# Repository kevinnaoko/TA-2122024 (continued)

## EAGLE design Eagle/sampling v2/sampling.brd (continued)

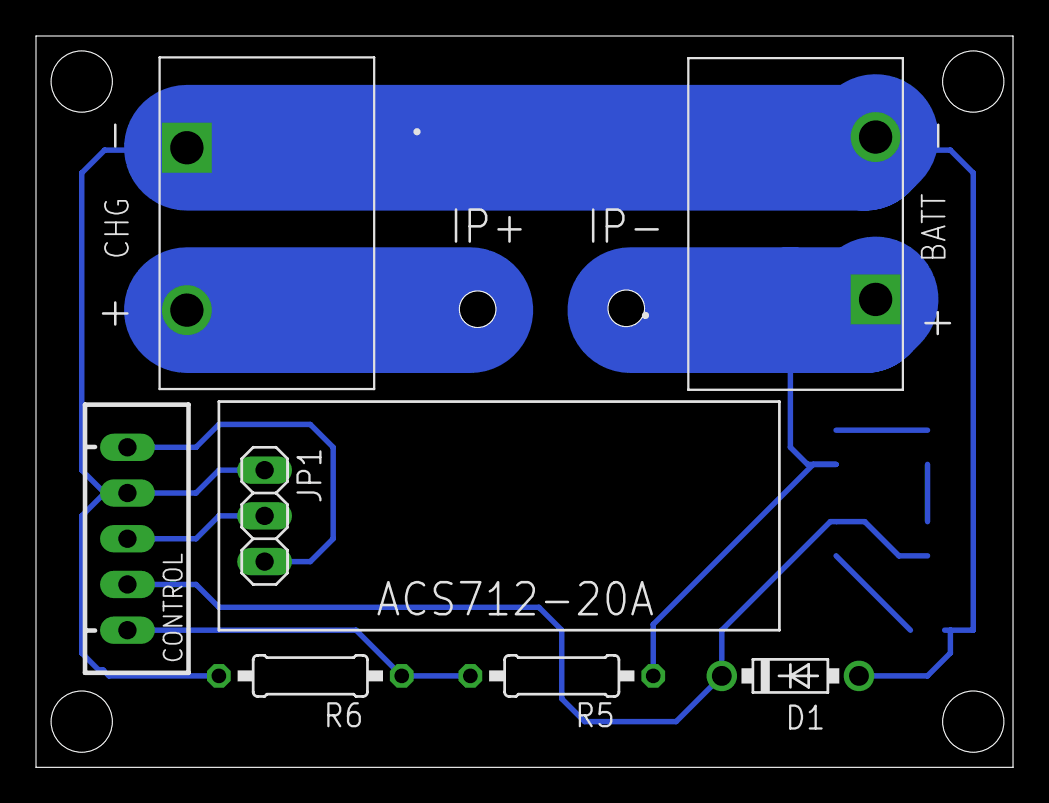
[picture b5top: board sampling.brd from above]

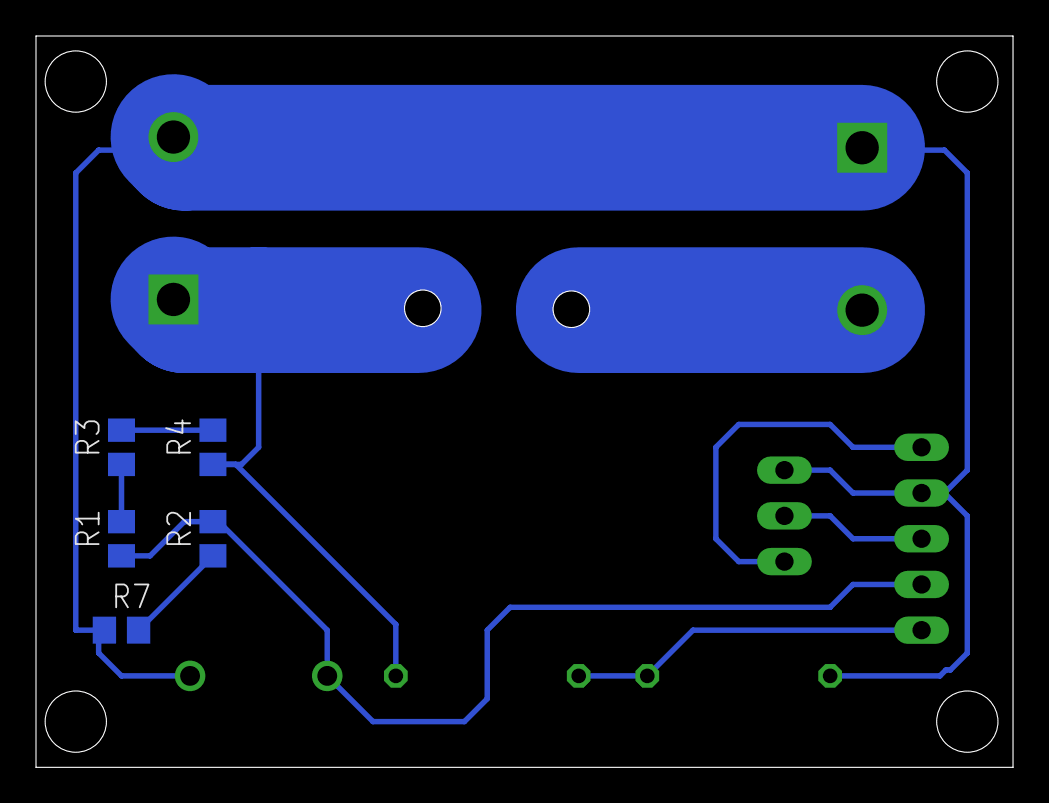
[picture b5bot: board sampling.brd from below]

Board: 2 copper layers, 54.3 x 40.6 mm, 12 parts (5 on the bottom side), 9 nets.

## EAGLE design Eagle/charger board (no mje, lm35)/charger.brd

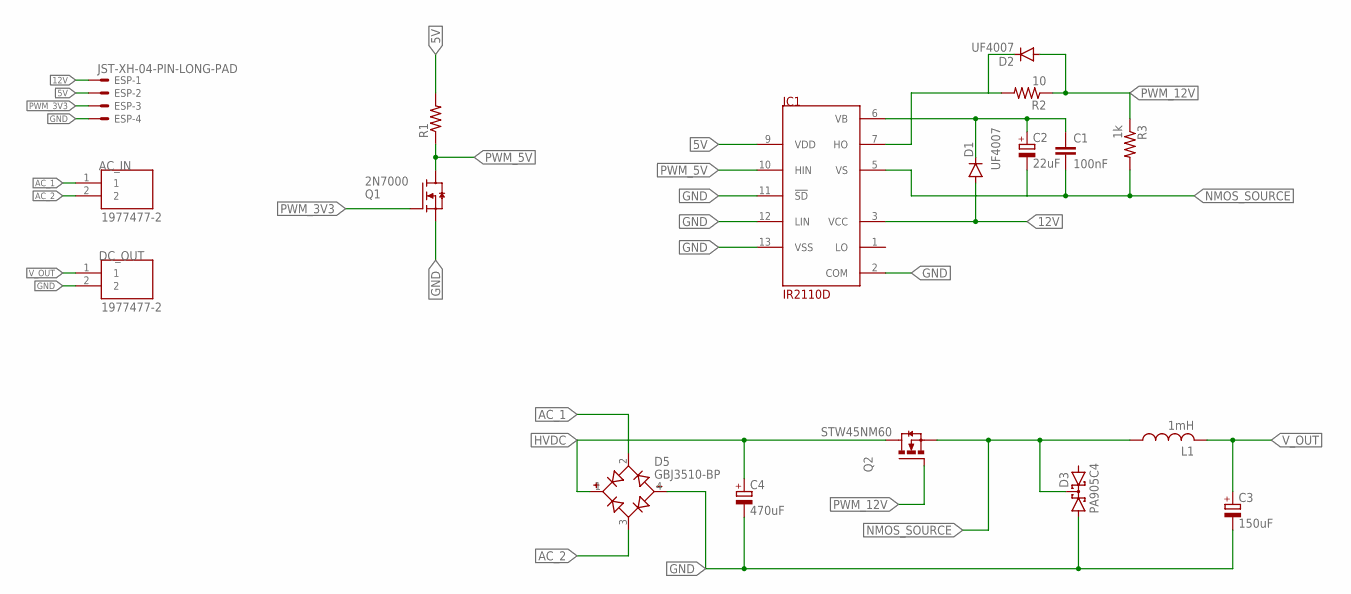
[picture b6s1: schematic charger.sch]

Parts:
AC_IN: 1977477-2; TE_1977477-2
C1: 100nF; C025-025X050
C2: 22uF; E2,5-6E
C3: 150uF; E7,5-18
C4: 470uF; EB35D
D1, D2: UF4007; DO34-7
D3: PA905C4; SOT93S
D5: GBJ3510-BP; DIOB_GBJ3510-BP
DC_OUT: 1977477-2; TE_1977477-2
ESP: JST-XH-04-PIN-LONG-PAD; JST-XH-04-PACKAGE-LONG-PAD
IC1: IR2110D; DIL14
L1: 1mH; TJ7-U1
Q1: 2N7000; TO92
Q2: STW45NM60; TO247AC
R1: R-US_0204/7; 0204/7
R2: 10; 0204/7
R3: 1k; 0204/7

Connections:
5V: ESP.2, IC1.9 (VDD), R1.2
12V: D1.A, ESP.1, IC1.3 (VCC)
AC_1: AC_IN.1, D5.2 (AC1)
AC_2: AC_IN.2, D5.3 (AC2)
GND: C3.-, C4.-, D3.A1, D5.4 (-), DC_OUT.2, ESP.4, IC1.2 (COM), IC1.11 (!SD), IC1.12 (LIN), IC1.13 (VSS), Q1.1 (S)
HVDC: C4.+, D5.1 (+), Q2.2 (D)
unnamed: D2.C, IC1.7 (HO), R2.2
NMOS_SOURCE: C1.2, C2.-, D3.C, IC1.5 (VS), L1.1, Q2.3 (S), R3.2
PWM_3V3: ESP.3, Q1.2 (G)
PWM_5V: IC1.10 (HIN), Q1.3 (D), R1.1
PWM_12V: D2.A, Q2.1 (G), R2.1, R3.1
VB: C1.1, C2.+, D1.C, IC1.6 (VB)
V_OUT: C3.+, DC_OUT.1, L1.2

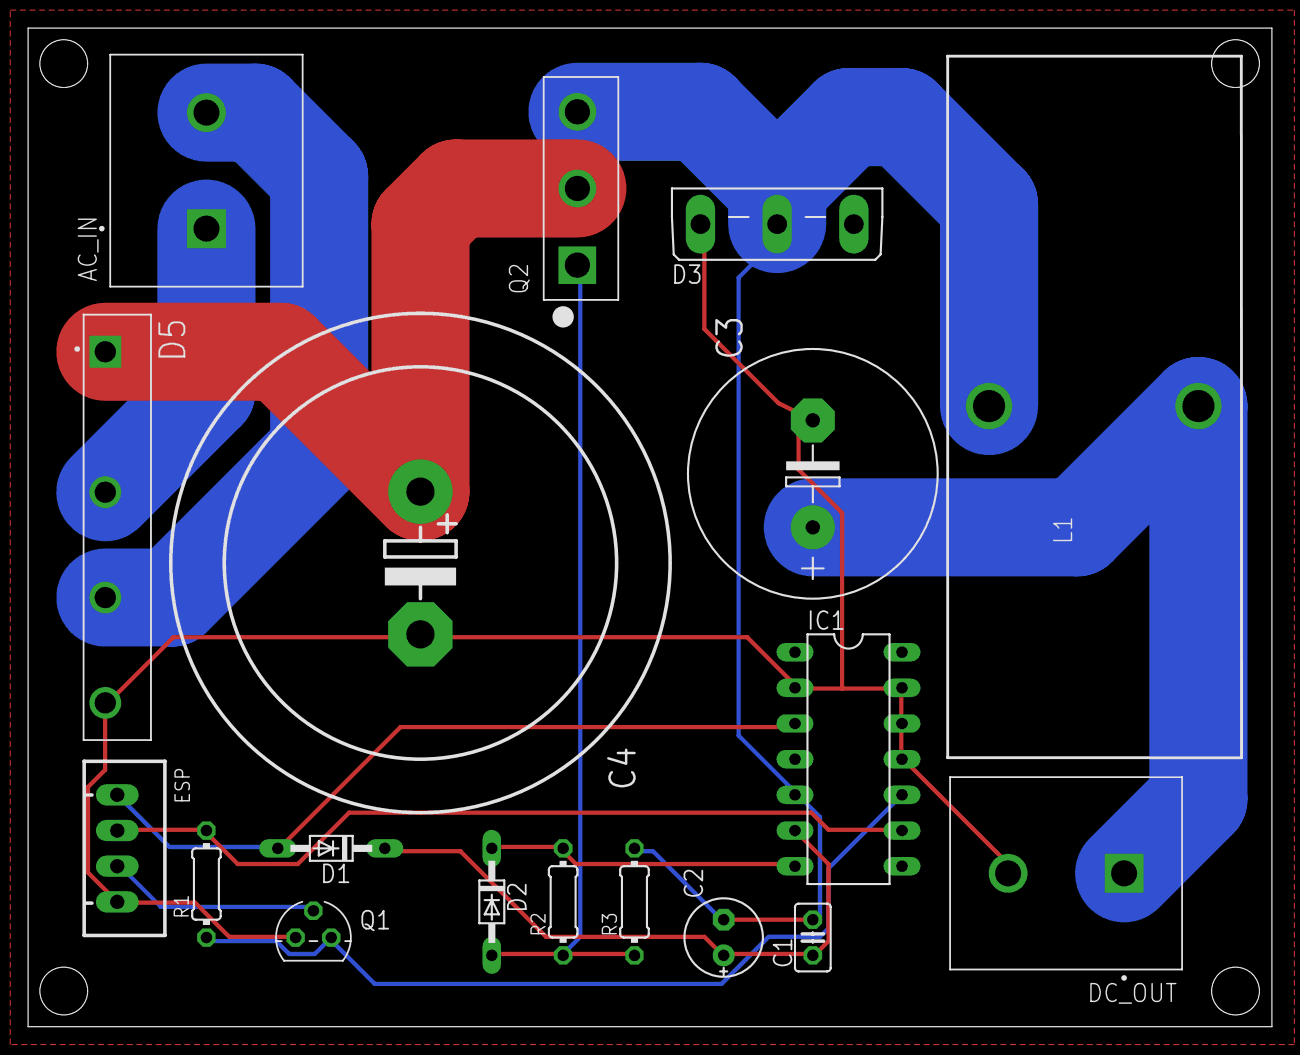
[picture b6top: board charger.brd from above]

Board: 2 copper layers, 88.6 x 71.1 mm, 18 parts (0 on the bottom side), 13 nets.

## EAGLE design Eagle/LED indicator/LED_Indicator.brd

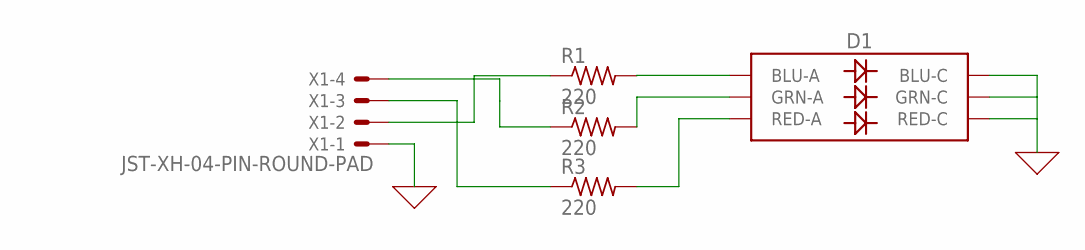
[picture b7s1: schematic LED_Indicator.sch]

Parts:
D1: LED-RGBBRG; LED-TRICOLOR-5050
R1, R2, R3: 220; R1206
X1: JST-XH-04-PIN-ROUND-PAD; JST-XH-04-PACKAGE-ROUND-PAD

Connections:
0: D1.1 (BLU-C), D1.2 (RED-C), D1.3 (GRN-C), X1.1
unnamed: D1.6 (BLU-A), R1.2
unnamed: D1.4 (GRN-A), R2.2
unnamed: D1.5 (RED-A), R3.2
unnamed: R1.1, X1.2
unnamed: R2.1, X1.4
unnamed: R3.1, X1.3

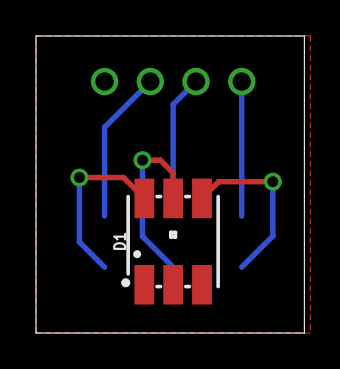
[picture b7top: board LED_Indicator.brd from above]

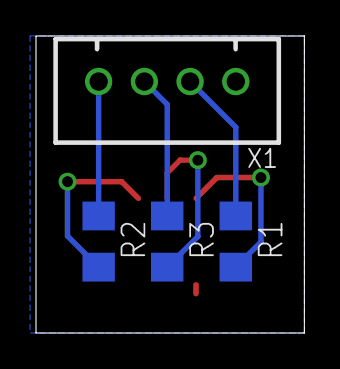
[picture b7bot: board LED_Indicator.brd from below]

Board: 2 copper layers, 14.9 x 16.5 mm, 5 parts (4 on the bottom side), 7 nets.

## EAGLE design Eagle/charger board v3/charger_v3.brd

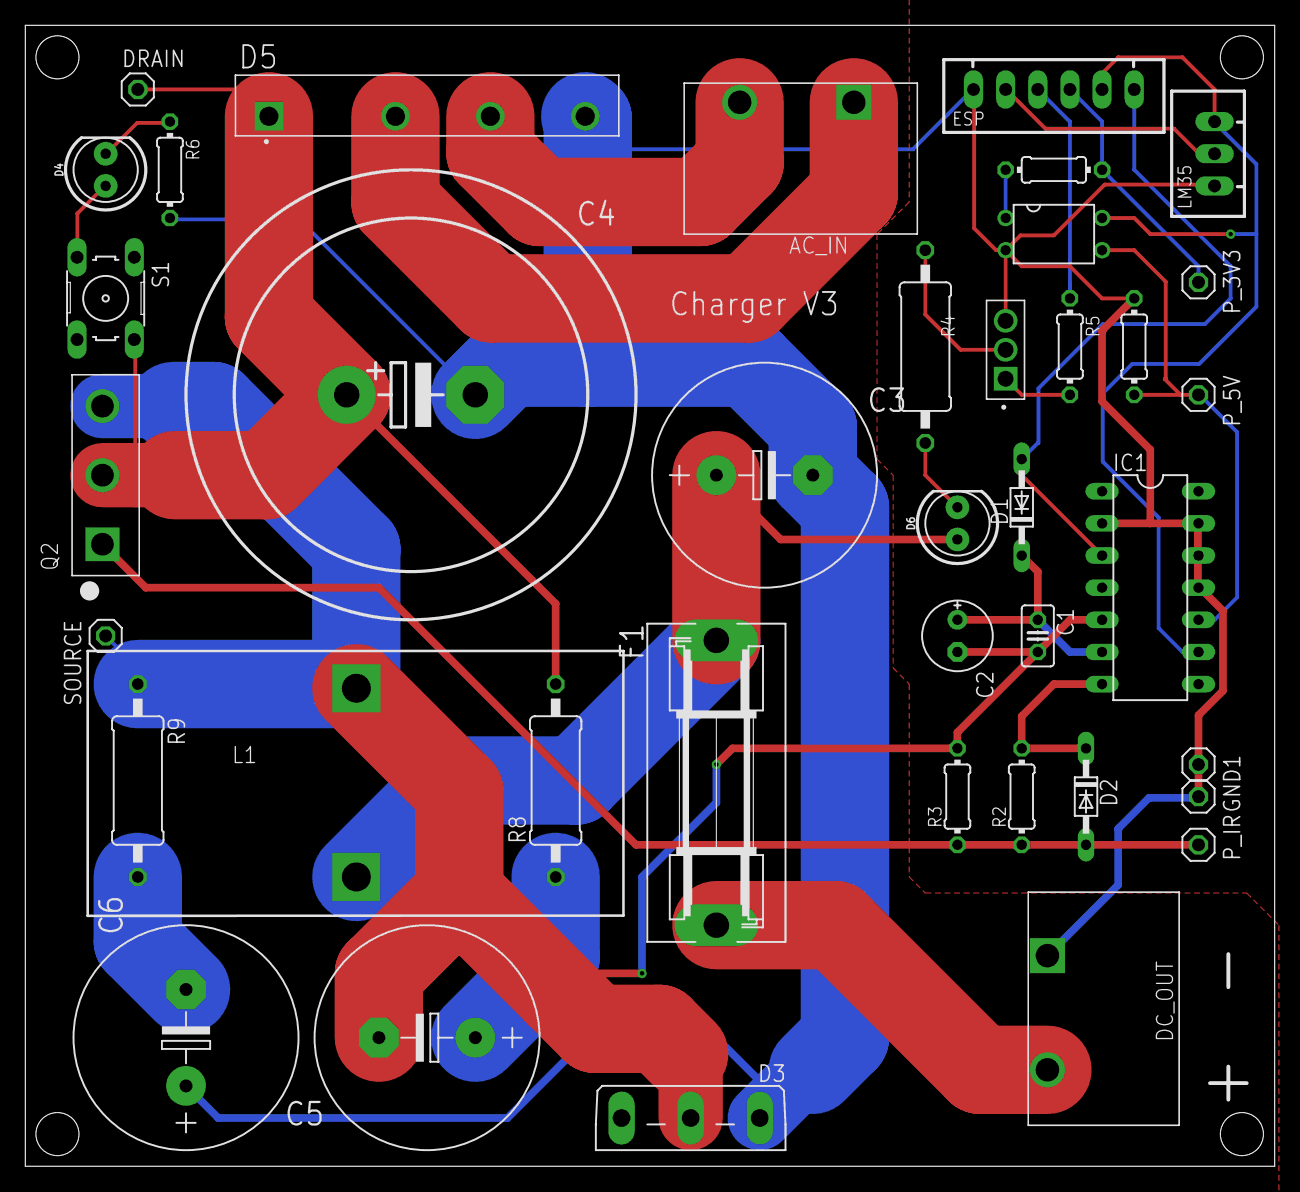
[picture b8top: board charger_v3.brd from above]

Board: 2 copper layers, 98.7 x 90.2 mm, 39 parts (0 on the bottom side), 24 nets.

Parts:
AC_IN: 1977477-2; TE_1977477-2
C1: 100nF; C025-025X050
C2: 22uF; E2,5-6E
C3: 150uF; E7,5-18
C4: 470uF; EB35D
C5, C6: 22uF; E7,5-18
D1, D2: UF4007; DO34-7
D3: PBYR3035; SOT93S
D4, D6: LED_5MM
D5: GBJ3510-BP; DIOB_GBJ3510-BP
DC_OUT: 1977477-2; TE_1977477-2
DRAIN: 1X01
ESP: JST-XH-06-PIN-LONG-PAD; JST-XH-06-PACKAGE-LONG-PAD
F1: FUSEHOLDER
GND1, GND2: 1X01
IC1: IR2110D; DIL14
L1: 1mH; TJ7-U1
LM35: JST-XH-03-PIN-LONG-PAD; JST-XH-03-PACKAGE-LONG-PAD
OK1: SFH618A-5; DIP4
P_3V3, P_5V: 1X01
P_IR: 1X01
Q2: IRFP240; TO247AC
Q3: MJE13003G; TO229P780X300X1364-3
R1: 180; 0204/7
R2: 10; 0204/7
R3, R7: 1k; 0204/7
R4: 68k; 0411/15
R5: 2.7k; 0204/7
R6: 10k; 0204/7
R8, R9: 31; 0411/15
S1: B3F-10XX
SOURCE: 1X01

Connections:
5V: ESP.2, IC1.9, LM35.3, OK1.4
12V: D1.A, ESP.1, IC1.3
AC_1: AC_IN.1, D5.2
AC_2: AC_IN.2, D5.3
GND: C3.-, C4.-, C6.+, D3.A1, D5.4, DC_OUT.1, ESP.6, GND1.1, GND2.1, IC1.2, IC1.11, IC1.12, IC1.13, LM35.1, OK1.2, Q3.3, R6.2, R7.1
HVDC: C4.+, D5.1, DRAIN.1, Q2.2, R8.2, S1.2
unnamed: D2.C, IC1.7, R2.2
unnamed: D4.A, S1.3
unnamed: Q3.2, R4.1
unnamed: D6.K, R4.2
unnamed: Q3.1, R5.2
unnamed: C5.+, R8.1
unnamed: C6.-, R9.2
unnamed: D4.K, R6.1
unnamed: OK1.1, R1.2
NMOS_SOURCE: C1.2, C2.-, C5.-, D3.C, IC1.5, L1.1, Q2.3, R3.2, R9.1, SOURCE.1
PWM_5V: IC1.10, OK1.3, P_5V.1, R7.2
PWM_12V: D2.A, P_IR.1, Q2.1, R2.1, R3.1
PWM_SW1: ESP.3, P_3V3.1, R1.1
PWM_SW2: ESP.4, R5.1
TEMP: ESP.5, LM35.2
VB: C1.1, C2.+, D1.C, IC1.6
V_OUT: C3.+, D6.A, F1.1, L1.2
V_OUT_FUSE: DC_OUT.2, F1.2

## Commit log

2022-03-31 push kode mqtt esp dan webserver
2022-03-31 Test push
2022-03-31 Udah ditambahin pengambilan data SOH dan SOC
2022-03-31 push Eagle dan rollback tanpa SoH
2022-04-02 update website
    add alerts
    user session
    manage users
2022-04-04 update dikit, push kode test buat vm
2022-04-04 ubah 2n700 ke opto + nambahin snubber di mosfet sama dioda
    ubah 2n700 ke opto + nambahin snubber di mosfet sama dioda
2022-04-04 routing v3
    routing v3: opto, snubber, momentary pb, fuse adjst
2022-04-04 benerin opto
    benerin opto
2022-04-04 reroute opto
2022-04-04 update board chg v3
    tambah probe buat D-S
2022-04-05 update board chg v3
    lebarin jalur, snubber
2022-04-05 update chg v3
    placement
2022-04-05 buat board charger v3.1
    spdt relay
2022-04-05 update board charger v3.1
    update gnd lolipop
2022-04-06 update chg v3.1
    relay ganti jadi songle 1ch lagi
2022-04-06 update sampling board
    zener, divider HV, update divider batt
2022-04-06 update chg v3.1
    benerin airwire, stubs
2022-04-06 push kode test standalone
    pwm cl + temp cutoff, gsm serial tx rx, dll
2022-04-07 push freertos_DEMO_gsm
    publish subscribe lewat gprs
2022-04-10 minor updates
2022-04-12 +Design casing
2022-04-18 bikin serverDb + freertos_gsm_test
2022-04-25 update eagle, server, esp
2022-04-25 ubah serial jadi serial1
    +nambahin kontrol v2
2022-04-25 UPdate kode b500
2022-04-26 update kode
2022-04-26 Charging berhenti berdasarkan arus
2022-04-28 edit kontrol v2
2022-04-28 librrary
2022-04-28 nambahin library eagle+update kontrolv2
2022-04-28 tambahin library ads
2022-04-28 Update board kontrol
    Harusnya sudah selesai
2022-04-29 Buat board charger V4
2022-04-29 Update routing charger v4
2022-04-29 Update kontrol
    XH8 -> xh10
    4p term -> 2p term x2
2022-04-29 minor update charger
2022-04-29 update kontrol
2022-04-30 update routing chg
2022-04-30 update charger
2022-05-07 gbr boards
2022-05-08 update webserver
    nambahin fitur view battery history, ubah ui main page sedikit
2022-05-09 update webserver
    Rapi rapiin css, bikin user friendly di handphone
2022-05-11 upload b500_test
2022-05-14 update control buat board baru
2022-05-14 update kode esp dan dahsboard
2022-05-14 minor fix database
2022-05-18 update dashboard
2022-06-02 update kode esp
    - task baru buat periodic batt data sampling
    - implementasi initial charging state delay 15s, periodic delay 1s
    - switch wifi/gprs lewat define
2022-06-03 minor fix dashboard
    tambahin advanced mode
2022-06-07 update beberapa kode
    - buat testbench_closedloop_v2
    - tambah sync initial enable di b500_v2
    - tambah listener topic sync initial enable di listenMqtt
    - driver tlp250 di charger v4_tlp
2022-06-10 update testbench
2022-06-10 nambahin poster
2022-06-10 update poster
2022-06-10 update poster dan brosur
2022-06-11 edit poster + lalalala
2022-06-12 tambah antisipasi pertanyaan
